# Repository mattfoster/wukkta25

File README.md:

# Wukkta 25 Badge

Features:

* BLE scanning for other badges
* User-specific splash images
* Interrupt driven MX switches with LEDs
* Charlieplexed LEDs
* Battery powered with USB-C charging
* 1.8" Round display (GC9A01)

Based on the SEEED XIAO ESP32-C3

## Hacking

Use Arduino.

Requires the esp32 Espressif board library, use version 2.0.14.

Requires a few libraries, via the library manager:

* TFT_eSPI (2.5.34, see compatibility note below)
* EasyButton (2.0.3)
* NimBLE Ardiono (2.3.6)
* PNGdec (1.1.6)

Some of these might have dependencies, and if they do you'll see errors.  

Select XIAO_ESP32C3 as the board, and it will appear as as `usbmodem` device on
a mac. 

### Suggestion

* Clean up my vibe coded mess.
* Write a macropad mode.
* Allow communications between badges.
* Add a decent AGENT.md with instructions on things like not using timers
inside of ISRs, and maybe including links to NimBLE's really good docs. 

## Display

The display is supported by TFT_eSPI, but there's a compatibility issue with
esp32 library versions above 2.0.14, where the board will hit a reboot loop.

On a mac, you'll need to populate `User_Setup.h` with board setup information,
and drop that in `~/Documents/Arduino/libraries/TFT_eSPI`. It's probably in
similar places on other platforms.

I'm the using the following, but I'm not sure where I got it:

```
#define USER_SETUP_ID 66

#define GC9A01_DRIVER  // Full configuration option, define additional parameters below for this display

#define TFT_RGB_ORDER TFT_RGB  // Colour order Blue-Green-Red
#define TFT_HEIGHT 240 // GC9A01 240 x 240

#define TFT_SCLK D8
#define TFT_MISO D9
#define TFT_MOSI D10
#define TFT_CS   D0  // Chip select control pin
#define TFT_DC   D1  // Data Command control pin
#define TFT_BL   D6
#define TFT_RST  -1  // Reset pin (could connect to RST pin)

#define LOAD_GLCD   // Font 1. Original Adafruit 8 pixel font needs ~1820 bytes in FLASH
#define LOAD_FONT2  // Font 2. Small 16 pixel high font, needs ~3534 bytes in FLASH, 96 characters
#define LOAD_FONT4  // Font 4. Medium 26 pixel high font, needs ~5848 bytes in FLASH, 96 characters
#define LOAD_FONT6  // Font 6. Large 48 pixel font, needs ~2666 bytes in FLASH, only characters 1234567890:-.apm
#define LOAD_FONT7  // Font 7. 7 segment 48 pixel font, needs ~2438 bytes in FLASH, only characters 1234567890:-.
#define LOAD_FONT8  // Font 8. Large 75 pixel font needs ~3256 bytes in FLASH, only characters 1234567890:-.
//#define LOAD_FONT8N // Font 8. Alternative to Font 8 above, slightly narrower, so 3 digits fit a 160 pixel TFT
#define LOAD_GFXFF  // FreeFonts. Include access to the 48 Adafruit_GFX free fonts FF1 to FF48 and custom fonts

#define SMOOTH_FONT

#define SPI_FREQUENCY 40000000
#define SPI_READ_FREQUENCY  20000000

```

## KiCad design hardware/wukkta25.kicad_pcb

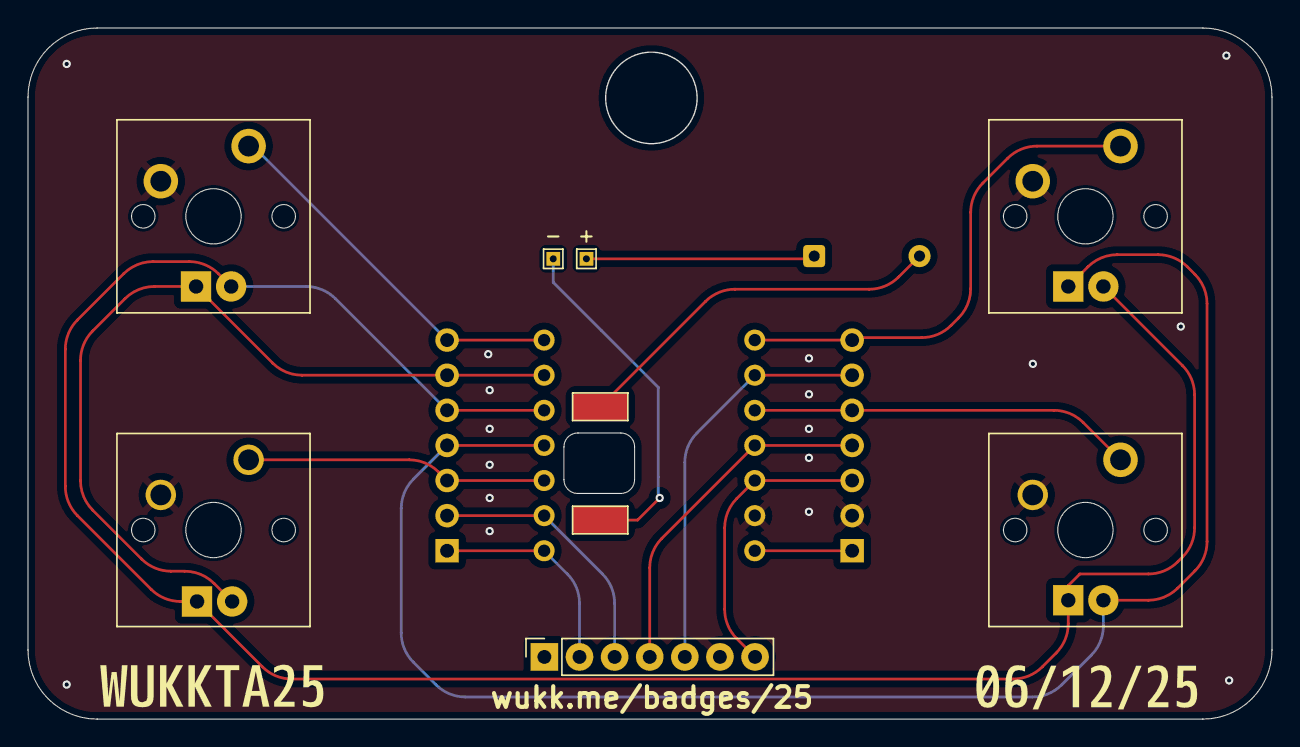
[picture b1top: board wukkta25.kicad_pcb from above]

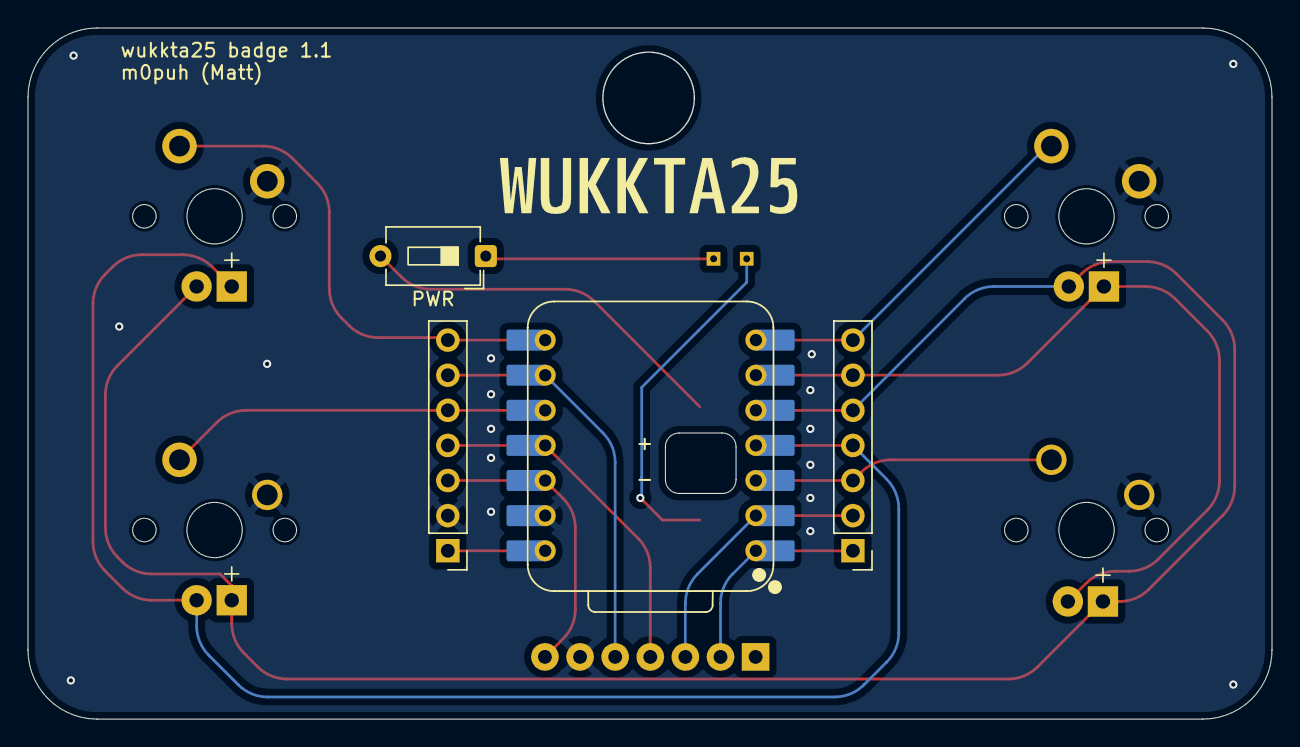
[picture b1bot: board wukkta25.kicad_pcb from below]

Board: 2 copper layers, 90.0 x 50.0 mm, 20 parts (5 on the bottom side), 16 nets.

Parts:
+: Conn_01x01_Pin; TestPoint_THTPad_1.0x1.0mm_Drill0.5mm
-: Conn_01x01_Pin; TestPoint_THTPad_1.0x1.0mm_Drill0.5mm
D1, D2, D3, D4: LED; MX-LED-PolarityMarked
J1: Conn_01x07_Socket; PinSocket_1x07_P2.54mm_Vertical
J2, J3: Conn_01x07_Socket; PinHeader_1x07_P2.54mm_Vertical
J5, J5#2: Conn_01x01_Pin; TestPoint_Pad_2.5x2.5mm
PWR: SW_SPST; SW_DIP_SPSTx01_Slide_6.7x4.1mm_W7.62mm_P2.54mm_LowProfile
SW1, SW2, SW3, SW4: SW_SPST; SW_Cherry_MX_1.00u_PCB
U1: XIAO-ESP32-C3-DIP; XIAO-ESP32C3-DIP
kibuzzard-68C1A562: G***; kibuzzard-68C1A562
kibuzzard-68C8464D: G***; kibuzzard-68C8464D
kibuzzard-68E80B3B: G***; kibuzzard-68E80B3B

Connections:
/CH1: D3.1 (K), D4.2 (A), J3.4, U1.4 (GPIO5/A3/D3)
/CH2: D1.2 (A), D2.1 (K), D3.2 (A), D4.1 (K), J3.5, U1.5 (GPIO6/D4/SDA)
/CH3: D1.1 (K), D2.2 (A), J3.6, U1.6 (GPIO7/D5/SCL)
/D0: J1.2 (CS), J3.1, U1.1 (GPIO2/A0/D0)
/D1: J1.3 (DC), J3.2, U1.2 (GPIO3/A1/D1)
/D2: J3.3, SW2.1 (A), U1.3 (GPIO4/A2/D2)
/D6: J3.7, SW4.1 (A), U1.7 (GPIO21/D6/TX)
/D7: J2.7, SW3.1 (A), U1.8 (GPIO20/D7/RX)
/D8: J1.5 (SCL), J2.6, U1.9 (GPIO8/D8/SCK)
/D9: J2.5, SW1.1 (A), U1.10 (GPIO9/D9/MISO)
/D10: J1.4 (SDA), J2.4, U1.11 (GPIO10/D10/MOSI)
/VBUS: J2.1, U1.14 (VBUS)
/VCC: J1.7 (VCC), J2.3, U1.12 (VCC_3V3)
GND: J1.6 (GND), J2.2, SW1.2 (B), SW2.2 (B), SW3.2 (B), SW4.2 (B), U1.13 (GND)
unnamed: +.1, PWR.1 (A)
unnamed: J5#2.1, PWR.2 (B)

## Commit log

2025-09-22 Initial commit of Wukkta25 radar themed badge
    All this does is handle graphics. It requires a custom user_setup and an
    old version of the ESP core library for compatibility with the TFT lib.
2025-10-03 Add experimental charlieplexed LEDs
2025-11-18 Add button function and image splash screen
2025-11-18 Use interrupts to read buttons
2025-11-29 Add BLE functionality using NimBLE
2025-11-30 Fix light flashing pattern
2025-11-30 Add image display
2025-11-30 Move scanning out of loop
2025-12-01 Fix scanning!
2025-12-04 Add per user images
2025-12-06 Add image and detection for sacha
2025-12-06 Add README and AGENTS docs
2025-12-06 Rearrage files
2025-12-06 Add hardware info
2025-12-07 Rename files for arduino happiness + clean up
2025-12-07 Add Amp generate macropad code
